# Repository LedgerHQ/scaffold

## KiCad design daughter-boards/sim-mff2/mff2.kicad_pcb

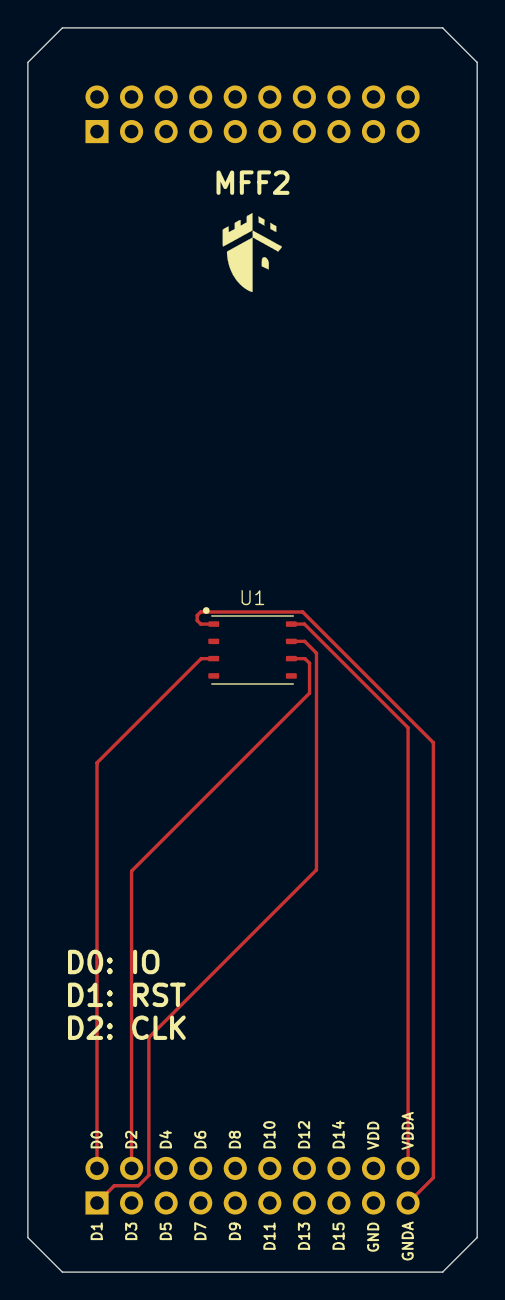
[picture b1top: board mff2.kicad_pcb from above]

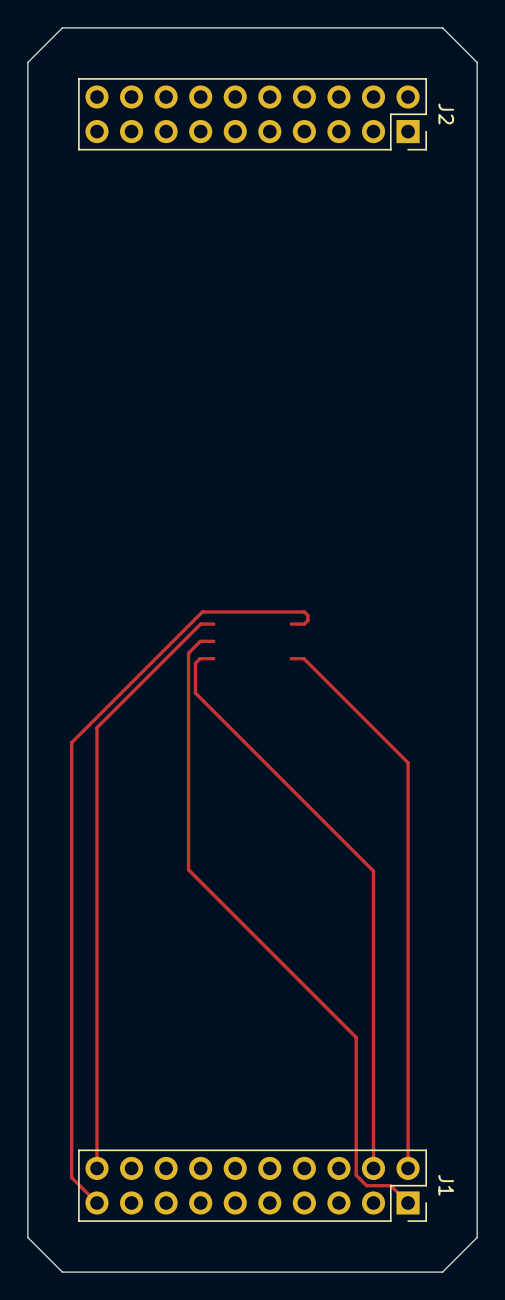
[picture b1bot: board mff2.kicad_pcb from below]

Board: 2 copper layers, 33.0 x 91.4 mm, 4 parts (2 on the bottom side), 5 nets.

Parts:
J1, J2: Conn_02x10_Odd_Even; PinSocket_2x10_P2.54mm_Vertical
LOGO1: DUNGEON_LOGO; donjon-2000
U1: MFF2_NO_EP

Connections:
+3V3: J1.20 (AVCC), U1.C1 (VCC)
GNDA: J1.19 (AGND), U1.C5 (GND)
unnamed: J1.2 (D0), U1.C7 (IO)
unnamed: J1.1 (D1), U1.C2 (RST)
unnamed: J1.4 (D2), U1.C3 (CLK)

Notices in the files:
daughter-boards/sim-mff2/mff2.kicad_pcb:
Under LGPL v3 license
